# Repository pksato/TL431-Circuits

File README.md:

# TL431-Circuits
Collection of Circuits using TL431 voltage regulator  
  
TL431_Fan_Control  
Using a 10k thermistor, 12V FAN is activated when temperature reach 50C.  
D1 (5v6 Zener) provide a stable reference voltage.  
Temperature is set selecting apropriente value of R3 (R6).  
  
TL431_OverVoltProt  
This circuit enagage relay when monitored voltage goes above 32VDC.  
R3 and R4 set the trip voltage.  
  
TL431_VoltageSupply  
Simple series voltage regulator.

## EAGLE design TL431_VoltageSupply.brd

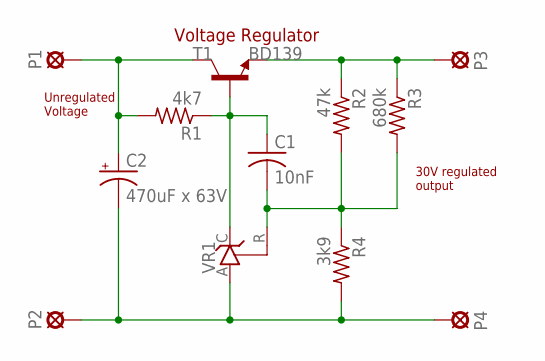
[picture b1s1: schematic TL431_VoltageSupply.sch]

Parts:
C1: 10nF; C050-024X044
C2: 470uF x 63V; E5-13
P1, P2, P3, P4: LSP10
R1: 4k7; 0207/10
R2: 47k; 0207/10
R3: 680k; 0207/10
R4: 3k9; 0207/10
T1: BD139; TO126
VR1: TL431CLP; TO92-CLP

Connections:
unnamed: P3.MP, R2.1, R3.1, T1.1 (E)
unnamed: C1.1, R1.1, T1.3 (B), VR1.C
unnamed: C1.2, R2.2, R3.2, R4.1, VR1.R
unnamed: C2.+, P1.MP, R1.2, T1.2 (C)
unnamed: C2.-, P2.MP, P4.MP, R4.2, VR1.A

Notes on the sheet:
Voltage Regulator
Unregulated Voltage
30V regulated output

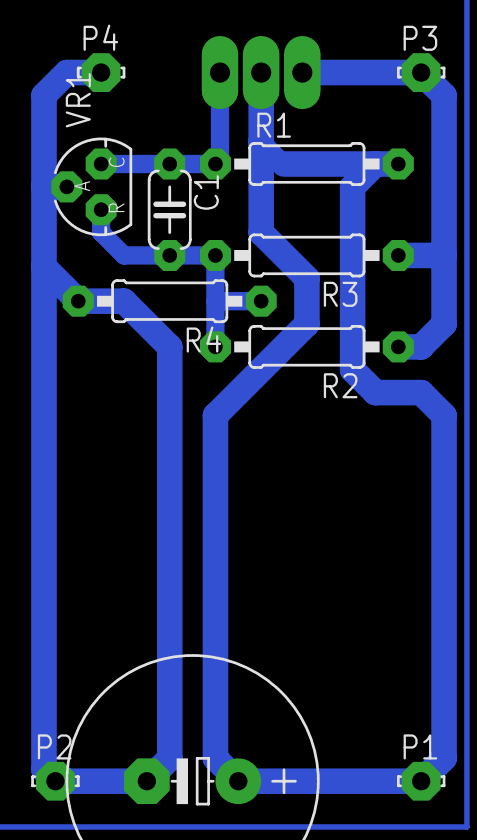
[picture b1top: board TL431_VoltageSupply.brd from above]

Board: 2 copper layers, 12 parts (1 on the bottom side), 5 nets.

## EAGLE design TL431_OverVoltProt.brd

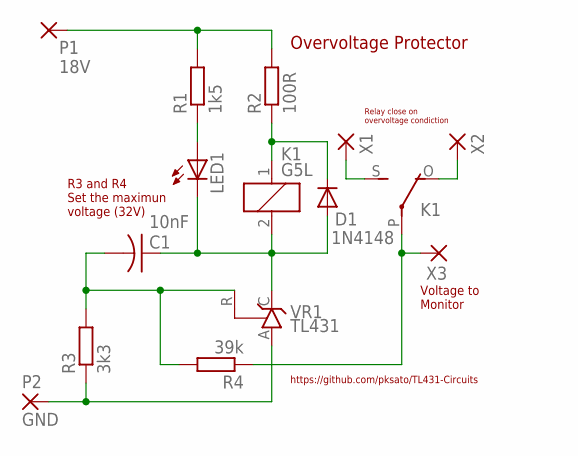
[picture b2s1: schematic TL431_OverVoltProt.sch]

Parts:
C1: 10nF; C050-024X044
D1: 1N4148; D-5
K1: G5L; G5LE
LED1: LED5MM
P1: 18V; 2,54/1,0
P2: GND; 2,54/1,0
R1: 1k5; 0207/10
R2: 100R; 0207/10
R3: 3k3; 0207/10
R4: 39k; 0207/10
VR1: TL431; TO92-CLP
X1, X2, X3: WIREPAD2,54/1,0; 2,54/1,0

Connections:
unnamed: K1.S, X1.1
unnamed: K1.O, X2.1
unnamed: K1.P, R4.1, X3.1
unnamed: D1.C, K1.1, R2.1
unnamed: C1.1, D1.A, K1.2, LED1.K (C), VR1.C
unnamed: LED1.A, R1.1
unnamed: C1.2, R3.2, R4.2, VR1.R
unnamed: P2.1, R3.1, VR1.A
unnamed: P1.1, R1.2, R2.2

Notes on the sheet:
Overvoltage Protector
Voltage to Monitor
R3 and R4 Set the maximun voltage (32V)
Relay close on overvoltage condiction
https://github.com/pksato/TL431-Circuits

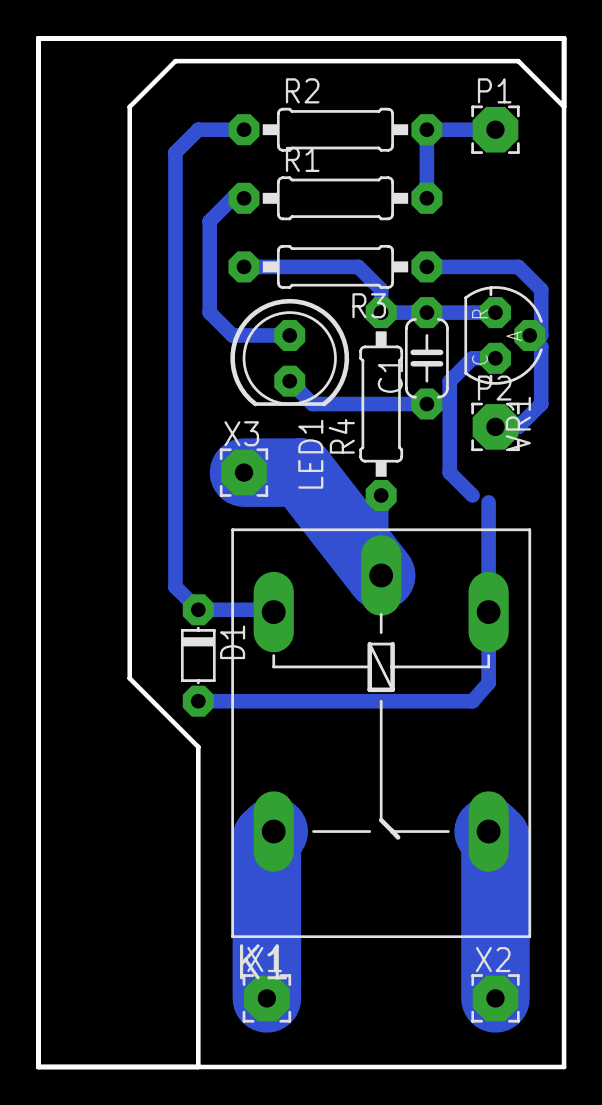
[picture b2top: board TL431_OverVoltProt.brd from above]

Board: 2 copper layers, 29.2 x 57.1 mm, 14 parts (0 on the bottom side), 9 nets.

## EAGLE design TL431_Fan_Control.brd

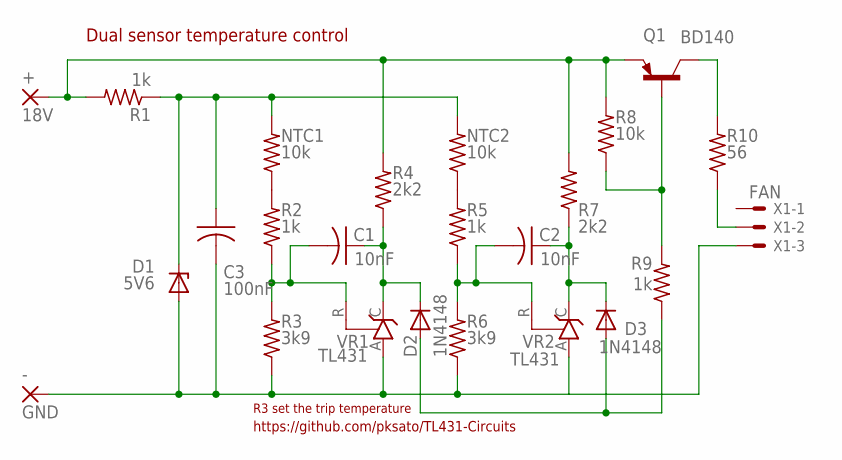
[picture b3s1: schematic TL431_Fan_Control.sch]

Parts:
+: 18V; 2,54/1,0
-: GND; 2,54/1,0
C1, C2: 10nF; C050-024X044
C3: 100nF; C050-024X044
D1: 5V6; ZDIO-7.5
D2, D3: 1N4148; D-5
NTC1, NTC2: 10k; 0207/2V
Q1: BD140; TO126
R1, R2, R5, R9: 1k; 0207/10
R3, R6: 3k9; 0207/10
R4, R7: 2k2; 0207/10
R8: 10k; 0207/10
R10: 56; 0617/22
VR1, VR2: TL431; TO92-CLP
X1: FAN; 22-23-2031

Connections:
unnamed: C3.1, D1.C, NTC1.2, NTC2.2, R1.1
unnamed: -.1, C3.2, D1.A, R3.1, R6.1, VR1.A, VR2.A, X1.3
unnamed: Q1.3 (B), R8.1, R9.2
unnamed: C1.2, R2.1, R3.2, VR1.R
unnamed: C2.2, R5.1, R6.2, VR2.R
unnamed: D2.A, D3.A, R9.1
unnamed: +.1, Q1.1 (E), R1.2, R4.2, R7.2, R8.2
unnamed: NTC1.1, R2.2
unnamed: NTC2.1, R5.2
unnamed: R10.1, X1.2
unnamed: Q1.2 (C), R10.2
unnamed: C2.1, D3.C, R7.1, VR2.C
unnamed: C1.1, D2.C, R4.1, VR1.C

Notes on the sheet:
Dual sensor temperature control
R3 set the trip temperature
https://github.com/pksato/TL431-Circuits

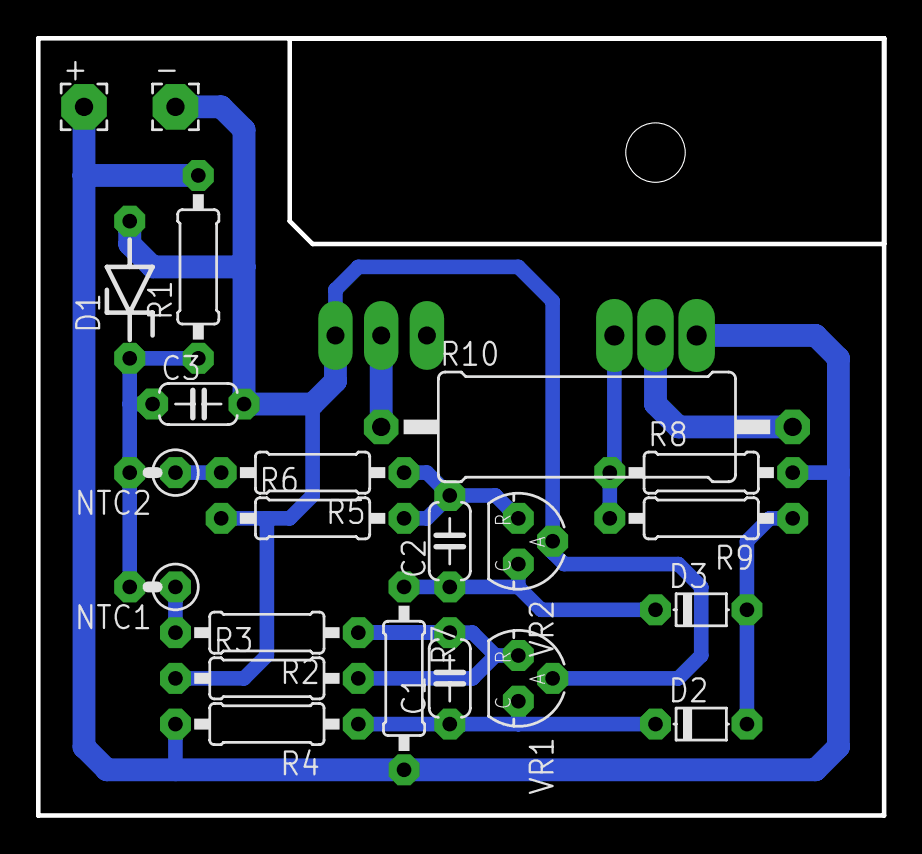
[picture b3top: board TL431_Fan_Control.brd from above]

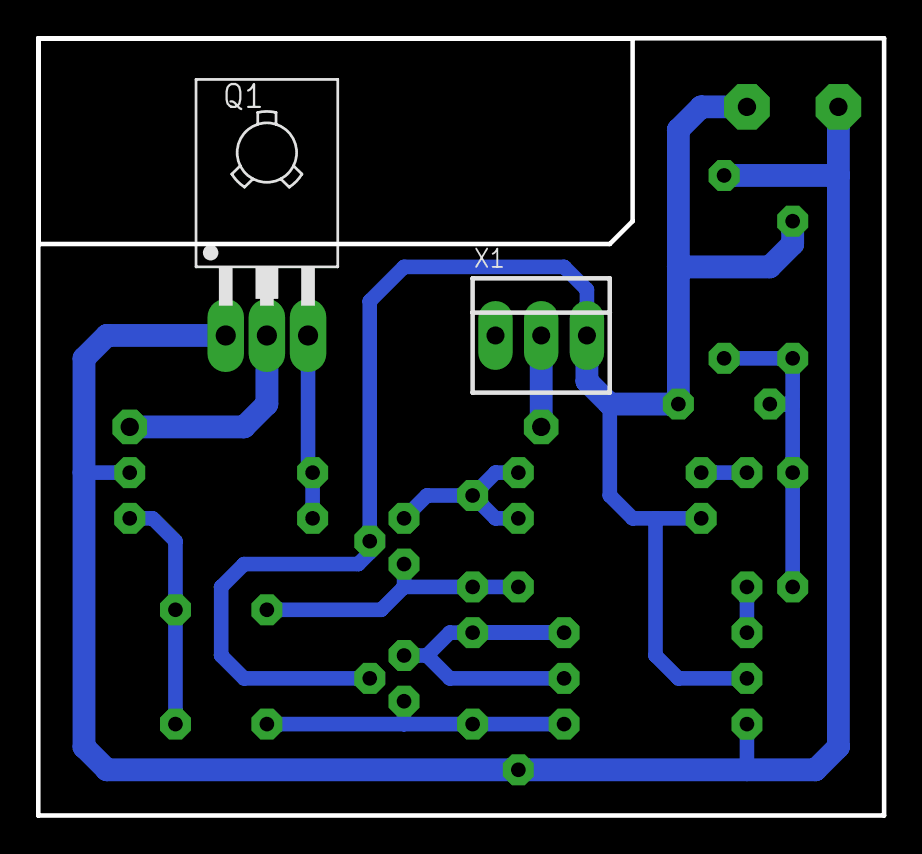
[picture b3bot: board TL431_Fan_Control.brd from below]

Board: 2 copper layers, 47.0 x 43.2 mm, 24 parts (2 on the bottom side), 13 nets.
